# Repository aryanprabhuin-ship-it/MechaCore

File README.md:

# MechaCore

MechaCore is my custom 60% (61 key) wired mechanical keyboard, its built around a **Raspberry Pi Pico 2** and a completely hand routed 2 layer PCB.

so basicaly i wanted to make a keyboard where i didnt just download somebody elses pcb and put switches in it.. i wanted to actualy understand the matrix, diodes, stabilizers, routing, plate tolerances and how the pcb fits inside a real printable case. i designed the layout, schematic, pcb and the full case from scratch using kicad + fusion 360 and ngl the case part took way more trys then i expected lol

## why i made this

i use a keyboard for school, coding and pretty much everything, but most custom boards i liked was either super expensive or still used a ready made pcb. making MechaCore was kinda my excuse to learn the full hardware pipeline instead of only assembling parts

main goals i set for myself :

- design a proper **60% ANSI PCB** in kicad with 61 switches
- wire the full matrix directly to a Raspberry Pi Pico 2
- hand route every row, column and diode connection on a real 2 layer board
- support screw-in stabilizers for backspace, enter, both shifts and the 6.25u spacebar
- make a rounded 3d printable bottom case + switch plate in fusion 360
- keep the files actualy manufacturable, not just make a nice looking render
- learn the full pipeline : keyboard layout -> schematic -> pcb -> 3d export -> case -> production files

the routing was easily the most painful bit because the board has 61 switches and basically no room for lazy paths 😭 after alot of moving tracks between front/back copper the pcb reached **0 unconnected items**, which felt kinda unreal after staring at ratsnest lines for so long

## project status

this repo has the full hardware design, cad, manufacturing exports and the Pico 2 firmware. the PCB and case geometry is done, the matrix pinout is locked and the firmware is ready to copy straight onto the controller. the current enclosure is **Rev D**, a two-piece fastenerless design with no screw heads or locator tips visible from the top

whats included :

- kicad project, schematic and fully routed pcb
- full 3d cad (`.f3d`, `.step` and printable `.stl` files)
- current Rev D fused bottom case and blind-snap switch plate exports
- retained Rev B and Rev C CAD archives for design-history / rollback
- production files (bom, positions, designators, ipc netlist and gerber zip)
- 60% ANSI keyboard layout json
- schematic and individual fabrication layer PDFs
- complete Pico 2 firmware with the matching CircuitPython UF2

current hardware summary :

| | |
|---|---|
| Layout | 60% ANSI, 61 keys |
| Controller | Raspberry Pi Pico 2 |
| Connectivity | wired USB through the Pico |
| Matrix | 14 columns x 5 rows, directly connected to the Pico |
| Diodes | 61x Slkor 1N4148W switching diodes, one per key (SOD-123, COL2ROW) |
| Stabilizers | Durock Clear screw-in V2 (6.25u space + 2u / 2.25u / 2.75u) |
| Switches | Akko V3 Penguin Pro |
| Keycaps | Plum Blossom cherry profile shine-through PBT |
| Case | 2 printed parts: fused bottom shell + blind-snap switch plate, no loose case hardware |
| PCB | 2 layer FR4, 300mm x 135.8mm, 1.6mm, green soldermask |
| Firmware | dependency free CircuitPython 10.2.1 USB HID firmware, 2 layers |

the dark rounded case and the big **MechaCore** name on the plate is what kinda gave the whole board its look. the pink plum blossom keycaps should contrast with it nicely, atleast thats the plan once it becomes a real physical board

## images

### current Rev D enclosure

the final top surface is continuous. all six screw stacks from the earlier revisions were removed and both kinematic locator receivers were made blind, so there are no fastener heads or locator dots visible around the key field

the bottom case still uses six reinforced mounting stations, dual load-spreader spines and the round/expansion datum system. the screw sockets are now undercut receivers for the fused plate collets

each plate lock has a split 3.6mm shaft, stepped insertion pilot and 4.3mm retention bead. the relief direction alternates around the plate to reduce sensitivity to print-axis anisotropy

the four hollow-cup feet, three PCB deflection catches and six underside ejector ports are fused into the two main printed bodies instead of being separate hardware

### PCB and electronics

the complete 14x5 matrix, all 61 switches, 61 diodes, stabilizer symbols and Pico connections are kept in the same KiCad project

### earlier enclosure development

these views show the original shell/plate work and are kept as design-history references. the Rev D files below are the current manufacturing set

## repository structure

```text
MechaCore/
├── 3D/
│   ├── Case/                 Fusion archives, STEP assemblies and case/plate STLs
│   └── PCB/                  PCB reference model exported as STEP and STL
├── BOM Pics/                 supplier/cart screenshots used during BOM research
├── firmware/                 CircuitPython firmware, boot setup and Pico 2 UF2
├── Images/                   README-ready project, PCB and CAD images
├── layout/                   60% ANSI keyboard-layout JSON
├── PCB/                      KiCad project, schematic, routed PCB and backups
├── PDFs/                     schematic plus individual fabrication-layer PDFs
├── production/               Gerbers, BOM, positions, designators and IPC netlist
├── Working screen shot/      working CAD captures, including Rev B, C and D views
├── bom.csv                   build-cost and purchase-planning BOM
└── README.md
```

`Images/` contains the curated screenshots used by this README. `Working screen shot/` keeps the corresponding working captures so the documentation images can be replaced or compared without opening Fusion or KiCad.

## repo file checklist

important current files in this repo :

- `PCB/Mechacore.kicad_pro`
- `PCB/Mechacore.kicad_sch`
- `PCB/Mechacore.kicad_pcb`
- `3D/Case/Mechacore-overengineered-revD.f3d`  (editable current enclosure)
- `3D/Case/Mechacore-overengineered-revD.step`  (current neutral CAD assembly)
- `3D/Case/Plate-blind-snap-revD.stl`  (print-ready plate with fused collets)
- `3D/Case/Bottom-case-fused-revD.stl`  (print-ready fused case)
- `3D/PCB/Mechacore.step`
- `3D/PCB/Mechacore.stl`
- `layout/keyboard-layout.json`
- `production/bom.csv`
- `production/positions.csv`
- `production/designators.csv`
- `production/netlist.ipc`
- `production/Mechacore.zip`  (gerbers)
- `bom.csv`  (build cost / purchase list)
- `PDFs/Mechacore.pdf`  (schematic print)
- `firmware/code.py`  (MechaCore key scanner + keymap)
- `firmware/boot.py`  (USB name + HID setup)
- `firmware/adafruit-circuitpython-raspberry_pi_pico2-en_US-10.2.1.uf2`

## cad

designed in **Fusion 360**. the current editable enclosure is `3D/Case/Mechacore-overengineered-revD.f3d`, with a STEP assembly beside it and separate production STLs for the case and plate

Rev D is intentionally overengineered while keeping the physical part count low. the Fusion timeline contains **289 items and 52 parameters**, but the finished enclosure is exactly **two printable solids** with no component/hardware occurrences:

- six fused, split snap collets on the plate underside
- six matching undercut sockets inside the reinforced case bosses
- 0.10mm radial retention interference and 0.05mm controlled seating travel
- alternating collet-split directions for print-anisotropy compensation
- round + expansion kinematic locators hidden below a 0.6mm plate roof
- six 1.2mm underside ejector ports for non-destructive service removal
- fused hollow-cup feet and fused PCB anti-sag catches
- existing wall gussets and dual load-spreader spines retained for the clamp/load path

to assemble it, align the blind locator pair and press evenly above the six edge stations until the retention beads seat in their undercut cavities. for removal, release the stations progressively through the underside ejector ports instead of bending one side of the plate

older CAD is intentionally kept in the same folder:

| Revision | Purpose |
|---|---|
| Original / unsuffixed | initial shell and plate baseline |
| Rev B | first proper six-point M2.5 screw mounting system |
| Rev C | screws, inserts, isolation washers, compression stops, feet and PCB supports |
| **Rev D** | current two-piece blind-snap design with fused service features |

the exact pcb was also exported as both STEP and STL in `3D/PCB/`. i used that model inside the case design instead of guessing the board outline, especially for the rounded corners, Pico usb opening, solder clearance and stabilizer holes

## firmware

firmware is finaly in the repo under `firmware/`. its a small dependency free CircuitPython setup written just for MechaCore, so theres no KMK folder, package install or placeholder pin list to fix later. the GPIO map was copied directly from the finished kicad PCB and the bundled UF2 is the official stable [CircuitPython Pico 2 build](https://circuitpython.org/board/raspberry_pi_pico2/)

| | |
|---|---|
| Runtime | CircuitPython 10.2.1 for Raspberry Pi Pico 2 |
| Rows | GP0, GP1, GP2, GP3, GP4 |
| Columns | GP5 through GP18 |
| Matrix | 5 rows x 14 columns, 61 populated positions |
| Diodes | column anode to row cathode (`columns_to_anodes=True`) |
| Debounce | 3 stable scans at 2ms, around 6ms total |
| USB | standard keyboard + consumer control HID |
| Rollover | 6 normal keys plus all modifiers |

the base layer follows the actual keycap layout :

```text
`     1   2   3   4   5   6   7   8   9   0   -   =   Backspace
Tab   Q   W   E   R   T   Y   U   I   O   P   [   ]   \
Caps  A   S   D   F   G   H   J   K   L   ;   '       Enter
Shift Z   X   C   V   B   N   M   ,   .   /           Shift
Ctrl  Win Alt             Space             Alt Win Menu/Fn Ctrl
```

the Menu key still works like a normal Menu key when tapped. hold it for 180ms or press it together with another key and it becomes Fn

- `Fn + backtick` = Escape
- `Fn + 1` through `Fn + =` = F1 through F12
- `Fn + Backspace` = Delete
- `Fn + U / I / O / P` = Home / Up / End / Page Up
- `Fn + J / K / L / ;` = Left / Down / Right / Page Down
- `Fn + Q / W / E` = Previous track / Play-Pause / Next track
- `Fn + M`, `Fn + ,`, `Fn + .`, `Fn + /` = Mute / Volume Down / Volume Up / Play-Pause

### flashing it

1. hold the BOOTSEL button on the Pico 2 while plugging the keyboard into usb
2. open the new `RP2350` drive and copy `firmware/adafruit-circuitpython-raspberry_pi_pico2-en_US-10.2.1.uf2` onto it
3. after it restarts as `CIRCUITPY`, copy `firmware/boot.py` and `firmware/code.py` to the root of that drive
4. unplug and reconnect once so the USB setup from `boot.py` loads cleanly

thats it, no pin edits or extra libraries are needed. the keyboard shows up as **MechaCore** and the files stay editable from the `CIRCUITPY` drive if i ever wanna change the layout later

## bom (summary)

full purchase list is in `bom.csv`. these prices are the rough planned cost in indian rupees, nothing was ordered yet

| # | Name | Purpose | Qty | Cost (₹) | Distributor | Link |
|---|------|---------|-----|----------|-------------|------|
| 1 | PCB fabrication | 2 layer MechaCore boards | 5 boards | 5288 | Robu | [Buy](https://robu.in/product/online-pcb-manufacturing-service/) |
| 2 | 3D printed case | bottom shell + plate | 1 set | own funded| Hack Club | — |
| 3 | Plum Blossom Cherry Profile Shine-Through PBT Keycap Set | keycaps to actualy type on | 1 set | own funded | Curiosity Caps | [Buy](https://curiositycaps.in/products/plum-blossom-cherry-profile-shine-through-dye-sublimation-pbt-keycap-set) |
| 4 | Durock Clear Screw-In Stabilizers V2 | keeps the large keys stable | 1 set | 1595 | StacksKB | [Buy](https://stackskb.com/store/durock-clear-screw-in-stabilizers-v2/?attribute_combination=7%2B1+Set&attribute_spacebar-size=6.25U) |
| 5 | Akko V3 Penguin Pro Switch (Pack of 45) | mechanical switches + spares | 1 pack | 1,199 | StacksKB | [Buy](https://stackskb.com/store/akko-v3-cream-black-pro-switch-pack-of-45/) |
| 6 | Raspberry Pi Pico 2 | microcontroller / the brains | 1 | 519 | Robu | [Buy](https://robu.in/product/raspberry-pi-pico-2/) |
| 7 | Slkor 1N4148W SOD-123 switching diodes | one diode per switch + some spares | 70 pcs | 100.10 | Robu | [Buy](https://robu.in/product/1n4148w-slkor-75v-1v-4ns-150ma-sod-123-switching-diodes-rohs/) |

**rough total bom cost : ₹8,701.10**

---

thanks for reading,, if you build one or spot something weird feel free to open a issue. this was my first full keyboard pcb + case made from scratch so its deffinately not perfect but i learnt a insane amount making it :)

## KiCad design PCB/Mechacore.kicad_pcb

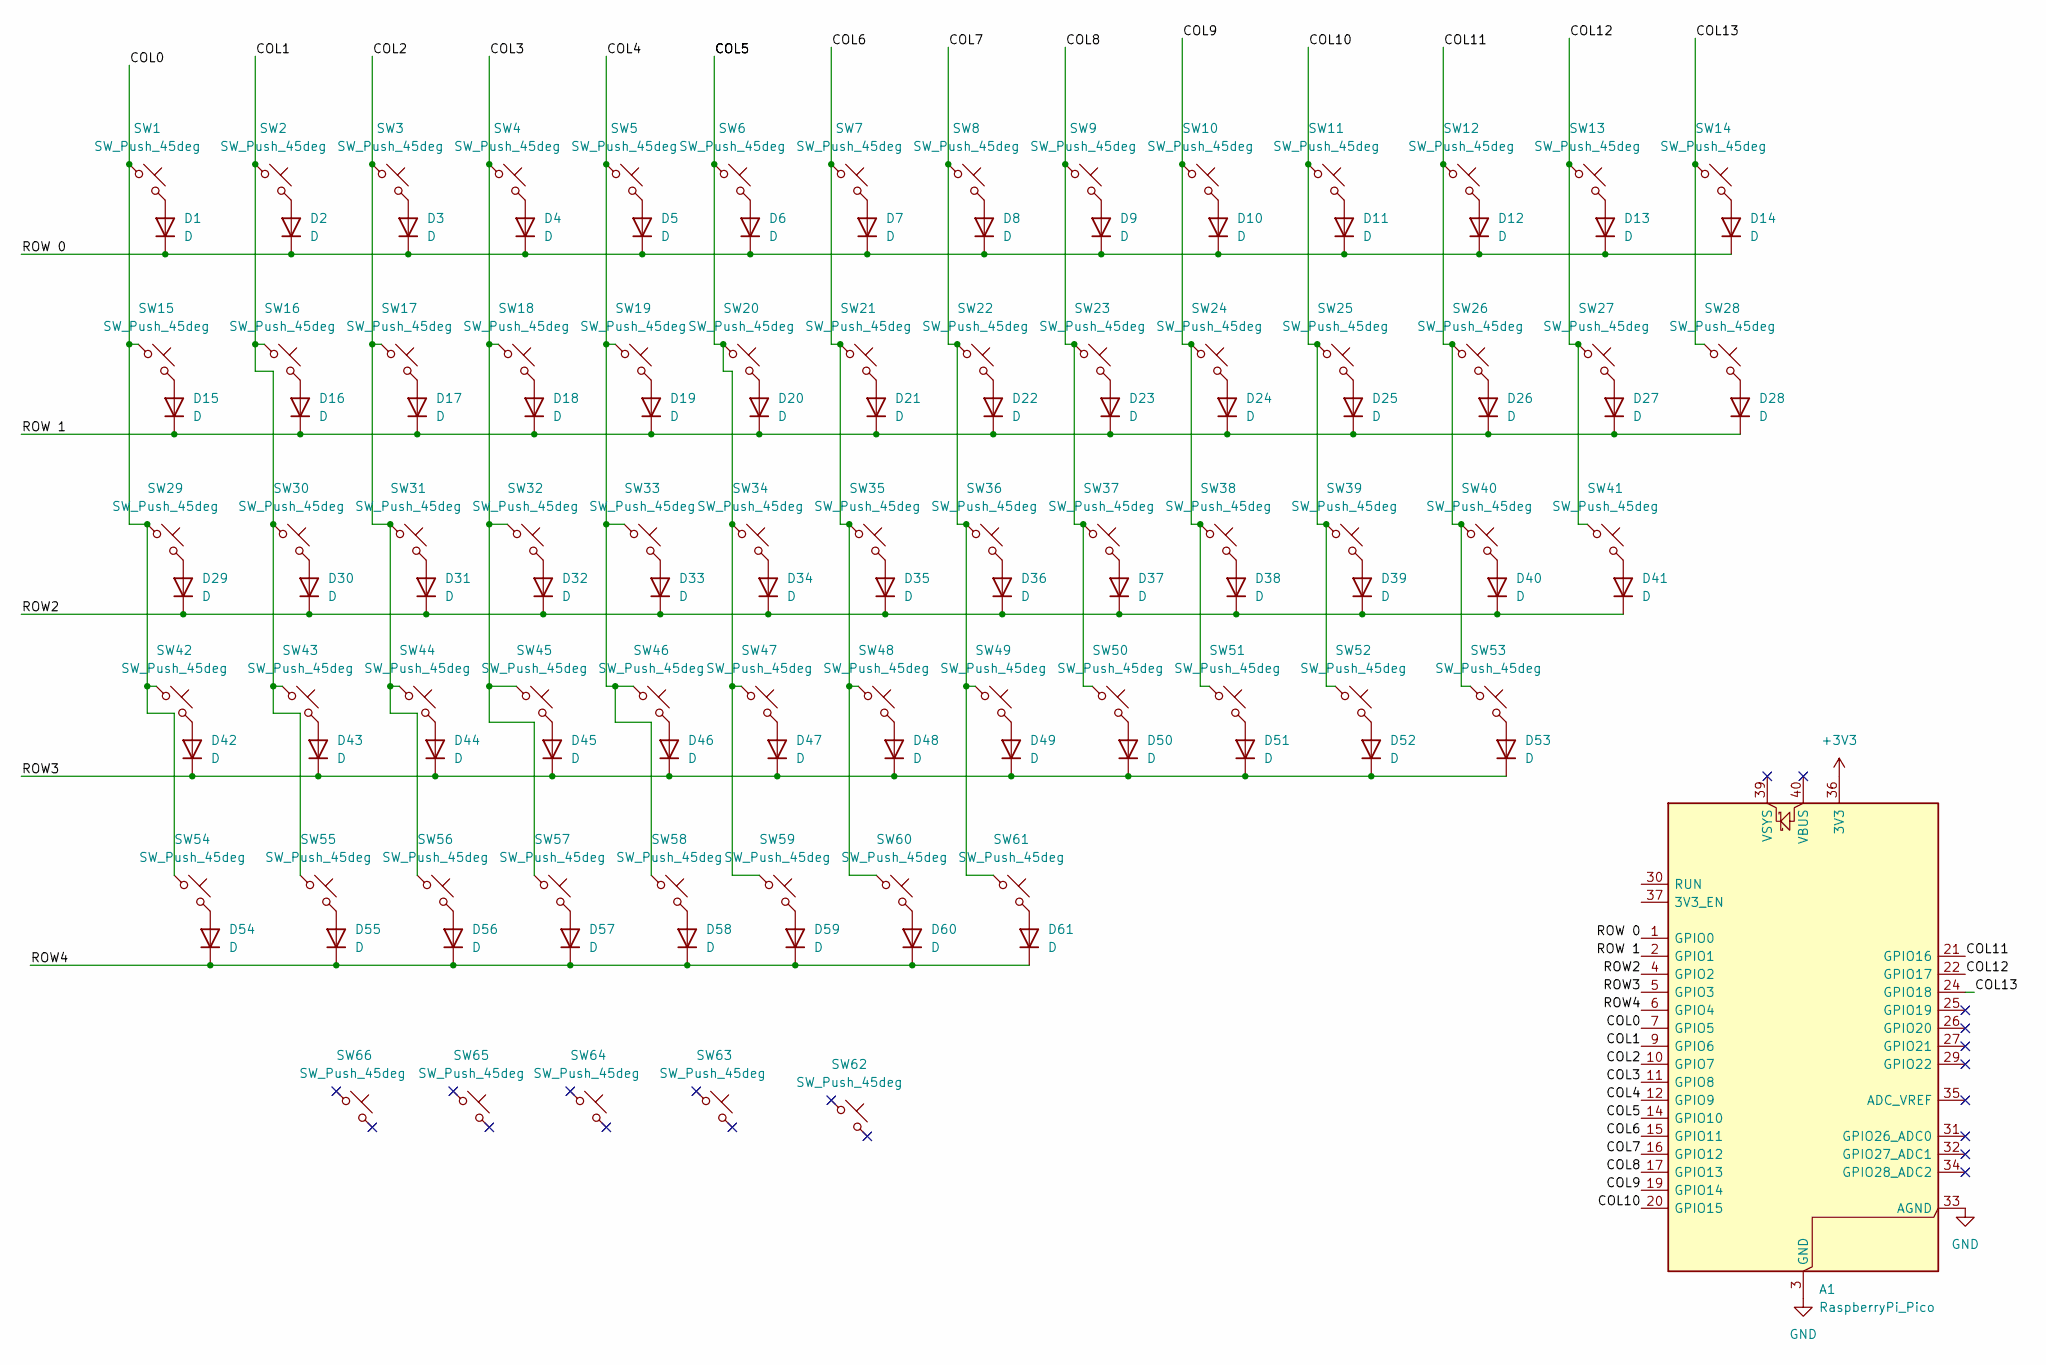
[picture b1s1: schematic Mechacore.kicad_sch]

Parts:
A1: RaspberryPi_Pico; RaspberryPi_Pico_Common_Unspecified
D1, D2, D3, D4, D5, D6, D7, D8, D9, D10, D11, D12, D13, D14, D15, D16, D17, D18, D19, D20, D21, D22, D23, D24, D25, D26, D27, D28, D29, D30, D31, D32, D33, D34, D35, D36, D37, D38, D39, D40, D41, D42, D43, D44, D45, D46, D47, D48, D49, D50, D51, D52, D53, D54, D55, D56, D57, D58, D59, D60, D61: D; D_SOD-123
SW1, SW2, SW3, SW4, SW5, SW6, SW7, SW8, SW9, SW10, SW11, SW12, SW13, SW16, SW17, SW18, SW19, SW20, SW21, SW22, SW23, SW24, SW25, SW26, SW27, SW30, SW31, SW32, SW33, SW34, SW35, SW36, SW37, SW38, SW39, SW40, SW43, SW44, SW45, SW46, SW47, SW48, SW49, SW50, SW51, SW52: SW_Push_45deg; SW_MX_1u
SW14: SW_Push_45deg; SW_Cherry_MX_PCB_2.00u
SW15, SW28: SW_Push_45deg; SW_MX_1.5u
SW29: SW_Push_45deg; SW_MX_1.75u
SW41, SW42: SW_Push_45deg; SW_Cherry_MX_PCB_2.25u
SW53: SW_Push_45deg; SW_Cherry_MX_PCB_2.75u
SW54, SW55, SW56, SW58, SW59, SW60, SW61: SW_Push_45deg; SW_MX_1.25u
SW57: SW_Push_45deg; SW_Cherry_MX_PCB_6.25u
SW62: SW_Push_45deg; STAB_MX_2u
SW63, SW64: SW_Push_45deg; STAB_MX_2.25u
SW65: SW_Push_45deg; STAB_MX_2.75u
SW66: SW_Push_45deg; STAB_MX_6.25u

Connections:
+3V3: A1.36 (3V3)
/COL0: A1.7 (GPIO5), SW1.1, SW15.1, SW29.1, SW42.1, SW54.1
/COL1: A1.9 (GPIO6), SW2.1, SW16.1, SW30.1, SW43.1, SW55.1
/COL2: A1.10 (GPIO7), SW3.1, SW17.1, SW31.1, SW44.1, SW56.1
/COL3: A1.11 (GPIO8), SW4.1, SW18.1, SW32.1, SW45.1, SW57.1
/COL4: A1.12 (GPIO9), SW5.1, SW19.1, SW33.1, SW46.1, SW58.1
/COL5: A1.14 (GPIO10), SW6.1, SW20.1, SW34.1, SW47.1, SW59.1
/COL6: A1.15 (GPIO11), SW7.1, SW21.1, SW35.1, SW48.1, SW60.1
/COL7: A1.16 (GPIO12), SW8.1, SW22.1, SW36.1, SW49.1, SW61.1
/COL8: A1.17 (GPIO13), SW9.1, SW23.1, SW37.1, SW50.1
/COL9: A1.19 (GPIO14), SW10.1, SW24.1, SW38.1, SW51.1
/COL10: A1.20 (GPIO15), SW11.1, SW25.1, SW39.1, SW52.1
/COL11: A1.21 (GPIO16), SW12.1, SW26.1, SW40.1, SW53.1
/COL12: A1.22 (GPIO17), SW13.1, SW27.1, SW41.1
/COL13: A1.24 (GPIO18), SW14.1, SW28.1
/ROW2: A1.4 (GPIO2), D29.1 (K), D30.1 (K), D31.1 (K), D32.1 (K), D33.1 (K), D34.1 (K), D35.1 (K), D36.1 (K), D37.1 (K), D38.1 (K), D39.1 (K), D40.1 (K), D41.1 (K)
/ROW3: A1.5 (GPIO3), D42.1 (K), D43.1 (K), D44.1 (K), D45.1 (K), D46.1 (K), D47.1 (K), D48.1 (K), D49.1 (K), D50.1 (K), D51.1 (K), D52.1 (K), D53.1 (K)
/ROW4: A1.6 (GPIO4), D54.1 (K), D55.1 (K), D56.1 (K), D57.1 (K), D58.1 (K), D59.1 (K), D60.1 (K), D61.1 (K)
/ROW 0: A1.1 (GPIO0), D1.1 (K), D2.1 (K), D3.1 (K), D4.1 (K), D5.1 (K), D6.1 (K), D7.1 (K), D8.1 (K), D9.1 (K), D10.1 (K), D11.1 (K), D12.1 (K), D13.1 (K), D14.1 (K)
/ROW 1: A1.2 (GPIO1), D15.1 (K), D16.1 (K), D17.1 (K), D18.1 (K), D19.1 (K), D20.1 (K), D21.1 (K), D22.1 (K), D23.1 (K), D24.1 (K), D25.1 (K), D26.1 (K), D27.1 (K), D28.1 (K)
GND: A1.3 (GND), A1.8 (GND), A1.13 (GND), A1.18 (GND), A1.23 (GND), A1.28 (GND), A1.33 (AGND), A1.38 (GND)
unnamed: D1.2 (A), SW1.2
unnamed: D2.2 (A), SW2.2
unnamed: D3.2 (A), SW3.2
unnamed: D4.2 (A), SW4.2
unnamed: D5.2 (A), SW5.2
unnamed: D6.2 (A), SW6.2
unnamed: D7.2 (A), SW7.2
unnamed: D8.2 (A), SW8.2
unnamed: D9.2 (A), SW9.2
unnamed: D10.2 (A), SW10.2
unnamed: D11.2 (A), SW11.2
unnamed: D12.2 (A), SW12.2
unnamed: D13.2 (A), SW13.2
unnamed: D14.2 (A), SW14.2
unnamed: D15.2 (A), SW15.2
unnamed: D16.2 (A), SW16.2
unnamed: D17.2 (A), SW17.2
unnamed: D18.2 (A), SW18.2
unnamed: D19.2 (A), SW19.2
unnamed: D20.2 (A), SW20.2
unnamed: D21.2 (A), SW21.2
unnamed: D22.2 (A), SW22.2
unnamed: D23.2 (A), SW23.2
unnamed: D24.2 (A), SW24.2
unnamed: D25.2 (A), SW25.2
unnamed: D26.2 (A), SW26.2
unnamed: D27.2 (A), SW27.2
unnamed: D28.2 (A), SW28.2
unnamed: D29.2 (A), SW29.2
unnamed: D30.2 (A), SW30.2
unnamed: D31.2 (A), SW31.2
unnamed: D32.2 (A), SW32.2
unnamed: D33.2 (A), SW33.2
unnamed: D34.2 (A), SW34.2
unnamed: D35.2 (A), SW35.2
unnamed: D36.2 (A), SW36.2
unnamed: D37.2 (A), SW37.2
unnamed: D38.2 (A), SW38.2
unnamed: D39.2 (A), SW39.2
unnamed: D40.2 (A), SW40.2
unnamed: D41.2 (A), SW41.2
unnamed: D42.2 (A), SW42.2
unnamed: D43.2 (A), SW43.2
unnamed: D44.2 (A), SW44.2
unnamed: D45.2 (A), SW45.2
unnamed: D46.2 (A), SW46.2
unnamed: D47.2 (A), SW47.2
unnamed: D48.2 (A), SW48.2
unnamed: D49.2 (A), SW49.2
unnamed: D50.2 (A), SW50.2
unnamed: D51.2 (A), SW51.2
unnamed: D52.2 (A), SW52.2
unnamed: D53.2 (A), SW53.2
unnamed: D54.2 (A), SW54.2
unnamed: D55.2 (A), SW55.2
unnamed: D56.2 (A), SW56.2
unnamed: D57.2 (A), SW57.2
unnamed: D58.2 (A), SW58.2
unnamed: D59.2 (A), SW59.2
unnamed: D60.2 (A), SW60.2
unnamed: D61.2 (A), SW61.2

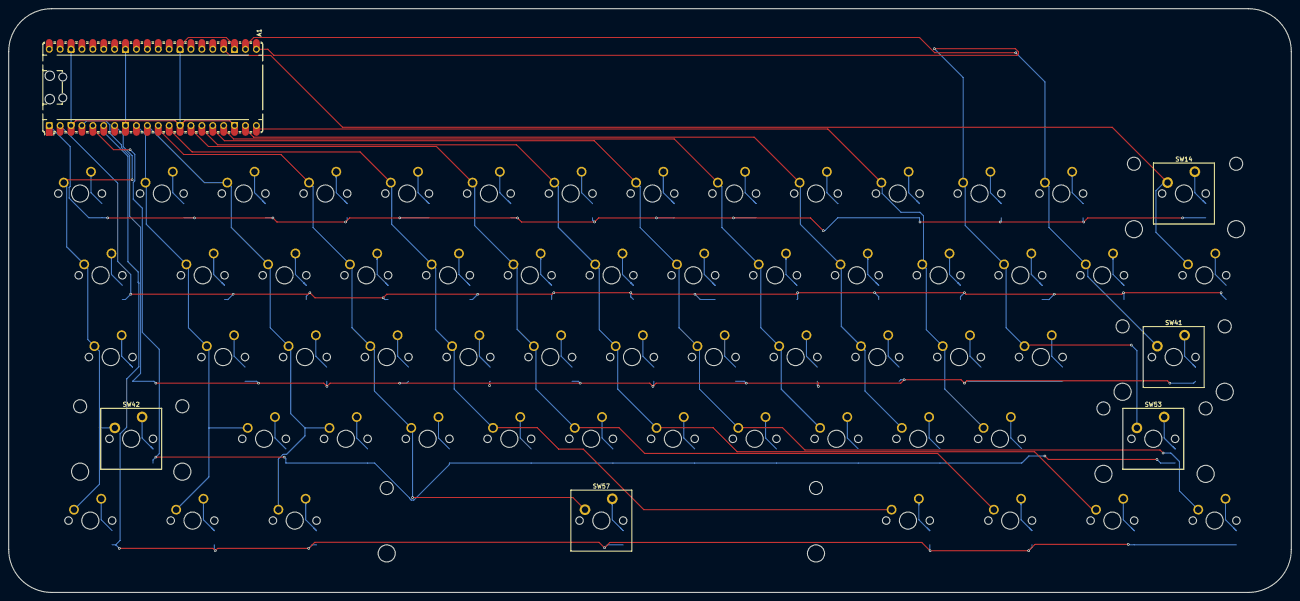
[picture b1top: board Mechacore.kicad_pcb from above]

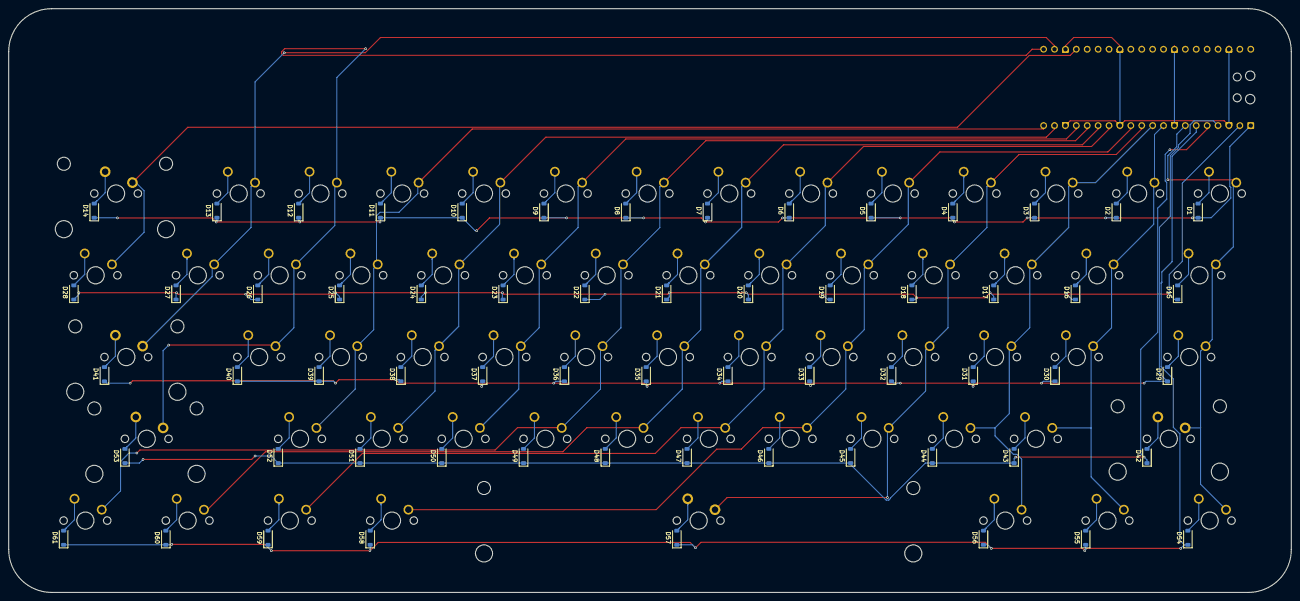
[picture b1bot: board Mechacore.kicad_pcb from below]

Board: 2 copper layers, 298.8 x 136.0 mm, 128 parts (61 on the bottom side), 81 nets.

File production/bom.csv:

Designator,Footprint,Quantity,Value,LCSC Part #
A1,RaspberryPi_Pico_Common_Unspecified,1,RaspberryPi_Pico,
"D1, D10, D11, D12, D13, D14, D15, D16, D17, D18, D19, D2, D20, D21, D22, D23, D24, D25, D26, D27, D28, D29, D3, D30, D31, D32, D33, D34, D35, D36, D37, D38, D39, D4, D40, D41, D42, D43, D44, D45, D46, D47, D48, D49, D5, D50, D51, D52, D53, D54, D55, D56, D57, D58, D59, D6, D60, D61, D7, D8, D9",D_SOD-123,61,1N4148W,
"SW1, SW10, SW11, SW12, SW13, SW16, SW17, SW18, SW19, SW2, SW20, SW21, SW22, SW23, SW24, SW25, SW26, SW27, SW3, SW30, SW31, SW32, SW33, SW34, SW35, SW36, SW37, SW38, SW39, SW4, SW40, SW43, SW44, SW45, SW46, SW47, SW48, SW49, SW5, SW50, SW51, SW52, SW6, SW7, SW8, SW9",SW_MX_1u,46,SW_Push_45deg,
SW14,SW_Cherry_MX_PCB_2.00u,1,SW_Push_45deg,
"SW15, SW28",SW_MX_1.5u,2,SW_Push_45deg,
SW29,SW_MX_1.75u,1,SW_Push_45deg,
"SW41, SW42",SW_Cherry_MX_PCB_2.25u,2,SW_Push_45deg,
SW53,SW_Cherry_MX_PCB_2.75u,1,SW_Push_45deg,
"SW54, SW55, SW56, SW58, SW59, SW60, SW61",SW_MX_1.25u,7,SW_Push_45deg,
SW57,SW_Cherry_MX_PCB_6.25u,1,SW_Push_45deg,
SW62,STAB_MX_2u,1,SW_Push_45deg,
"SW63, SW64",STAB_MX_2.25u,2,SW_Push_45deg,
SW65,STAB_MX_2.75u,1,SW_Push_45deg,
SW66,STAB_MX_6.25u,1,SW_Push_45deg,
